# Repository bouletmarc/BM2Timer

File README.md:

# BM2Timer

This little gem plugs into your 28-pin socket that normally takes a 27C256 chip.

This is used to put two tuning files of 32kb on a 64kb chip (XXX512 chip) and switch between one or the other tune file.

The BM2Timer V1.1 (and newer) has 2 methods for changing between tunes:
- Blue 2Pin Jumper (method which requires no additional equipment)
- External switch (method which requires a switch *not included*)

**Blue 2Pin Jumper Method**

With this Method you simply need to move the 2Pin blue jumper from pins 1-2 to pins 2-3 to switch between the two tunes.
- When the jumper is on the pins 1-2, it's for tune #2 (use 0000 to 7FFF chip region)
- When the jumper is on the pins 2-3, it's for tune #1 (use 8000 to FFFF chip region)

**External Switch Method**

It can has a single wire lead coming off of it using the middle pin (pin #2).
- When sorting this wire to ground you will run on the tune #2.
If this wire is in open circuit (not connect to ground or any source), it will be on tune #1.

# [Clic HERE to Obtain the BM2Timer][]

**Simple Connection 'Diagram' when using External Switch:**

Middle pin (Pin#2) -> Wire -> Switch (one end)

Switch (other end) -> Ground

The switch must be a toggle switch (SPST or SPDT) if you want to switch from one tune to another without holding the button, otherwise if you want to change tune only when the button is held, use a momentary switch.

# COMPATIBLE CHIPS

- 27C512
- W27C512
- W27E512
- 27SF512 SST
- XXX512

This is the requirement if the model you use aren't listed above:

Any 28pin Chips that end by (or has) the '512' marking on them, that are '64kb X8' and that the Pin #1 represent 'A15' will works.

If it has the 512 marking (its also a 64kb X8 chip) but the pin #1 doesn't represent A15 it'll not be a compatible chip!

# ADDRESSING INFORMATIONS

- The first Tune are using chip addressing 8000-FFFF
- The second Tune are using chip addressing 0000-7FFF

# HOW TO BURN A CHIP FOR THE BM2Timer

With the software that goes with your eprom programmer (chip burner), you will start by selecting your chip model.

1. Erase the chip (if it is blank avoid this step)
2. Open your Tune #2 file (yes #2)
3. Burn this file from 0000 to 7FFF
4. Then open your Tune #1
5. Burn this file from 8000 to FFFF
6. Now your chip is ready to be used, it includes your two files!

# Parts List to build your BM2Timer PCB

- 1x 10K Ohms 1/6w Resistor(Can be almost any value actually, doesn't need to be perfectly 10K Ohms)
- 1x 2Pins Jumper
- 1x Female Jumper Wire(Only if you use Extrenal Button switch)
- 1x 3Pins Male Angle Header**
- 2x 14Pins Male to Male Round pin header**
- 2x 14Pins Male to Female Header** OR 1x 28Pins DIP Socket

****These parts usually come in 40Pins rows that you have to cut to the desired lenght**

# BM2Timer V1.1

# Circuit Schematic Diagram 

[Clic HERE to Obtain the BM2Timer]:<https://bmdevs.fwscheckout.com/product/bm2timer>

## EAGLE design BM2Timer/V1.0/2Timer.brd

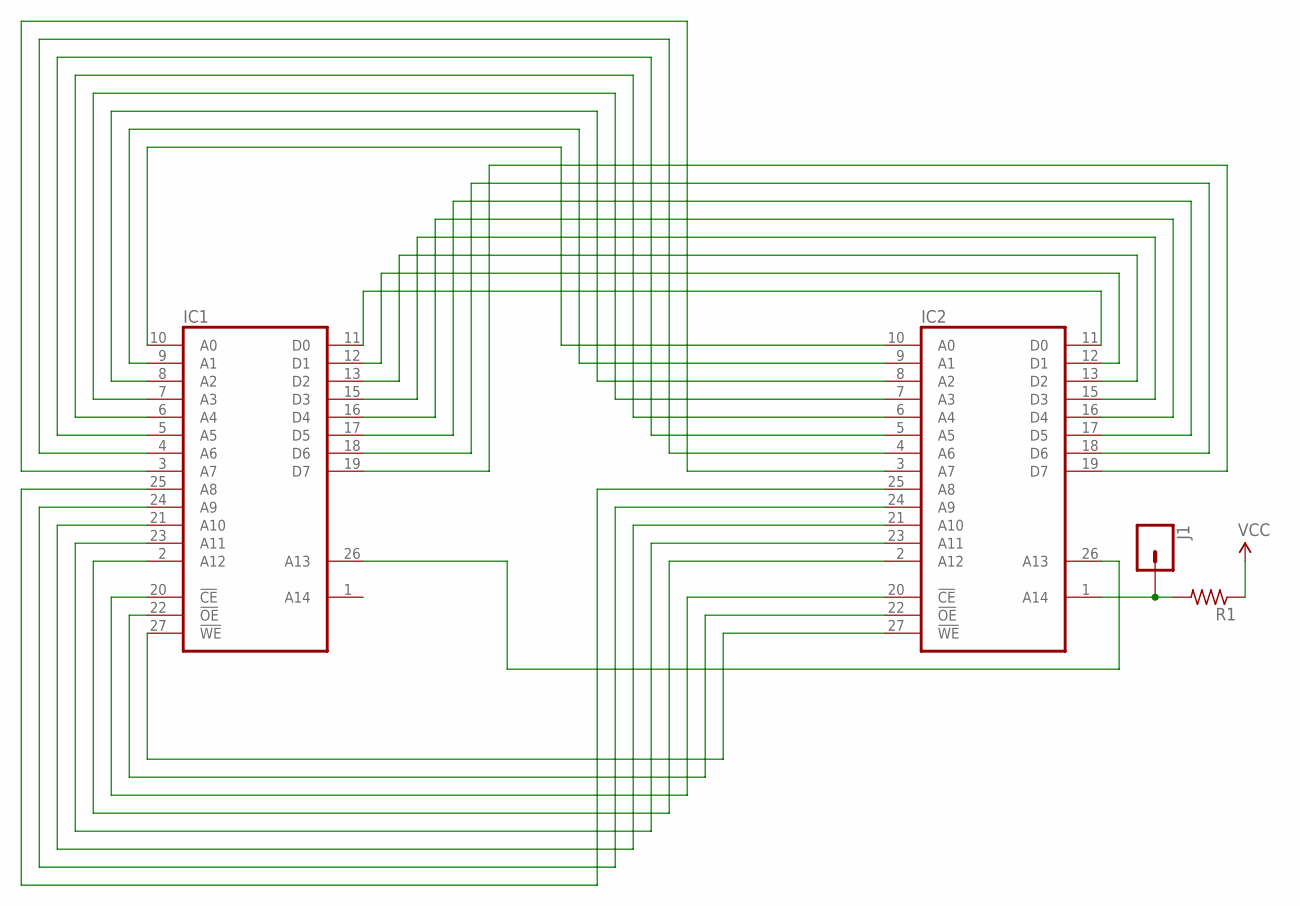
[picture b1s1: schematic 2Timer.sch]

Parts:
IC1, IC2: 2864; DIL28
J1: CONN_01; 1X01
R1: R-US_0204/5; 0204/5

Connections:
GND: IC1.14 (GND), IC2.14 (GND)
unnamed: IC1.20 (!CE), IC2.20 (!CE)
unnamed: IC1.11 (D0), IC2.11 (D0)
unnamed: IC1.12 (D1), IC2.12 (D1)
unnamed: IC1.13 (D2), IC2.13 (D2)
unnamed: IC1.23 (A11), IC2.23 (A11)
unnamed: IC1.15 (D3), IC2.15 (D3)
unnamed: IC1.16 (D4), IC2.16 (D4)
unnamed: IC1.17 (D5), IC2.17 (D5)
unnamed: IC1.18 (D6), IC2.18 (D6)
unnamed: IC1.19 (D7), IC2.19 (D7)
unnamed: IC1.26 (A13), IC2.26 (A13)
unnamed: IC1.10 (A0), IC2.10 (A0)
unnamed: IC1.9 (A1), IC2.9 (A1)
unnamed: IC1.8 (A2), IC2.8 (A2)
unnamed: IC1.7 (A3), IC2.7 (A3)
unnamed: IC1.6 (A4), IC2.6 (A4)
unnamed: IC1.5 (A5), IC2.5 (A5)
unnamed: IC1.4 (A6), IC2.4 (A6)
unnamed: IC1.3 (A7), IC2.3 (A7)
unnamed: IC1.25 (A8), IC2.25 (A8)
unnamed: IC1.24 (A9), IC2.24 (A9)
unnamed: IC1.2 (A12), IC2.2 (A12)
unnamed: IC1.21 (A10), IC2.21 (A10)
unnamed: IC1.22 (!OE), IC2.22 (!OE)
unnamed: IC1.27 (!WE), IC2.27 (!WE)
unnamed: IC2.1 (A14), J1.1, R1.2
VCC: IC1.28 (VCC), IC2.28 (VCC), R1.1

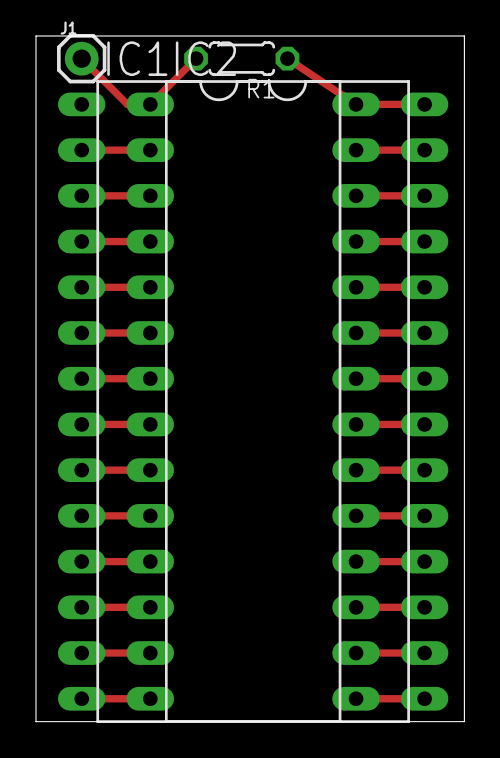
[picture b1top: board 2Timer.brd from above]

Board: 2 copper layers, 23.8 x 38.1 mm, 4 parts (0 on the bottom side), 28 nets.

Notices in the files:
parts and their libraries:
SparkFun-Connectors: Licensing: Creative Commons ShareAlike 4.0 International - https://creativecommons.org/licenses/by-sa/4.0
SparkFun: Licensing: CC v3.0 Share-Alike You are welcome to use this library for commercial purposes.
